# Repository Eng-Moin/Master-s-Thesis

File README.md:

# Master-s-Thesis

[Master-s-Thesis

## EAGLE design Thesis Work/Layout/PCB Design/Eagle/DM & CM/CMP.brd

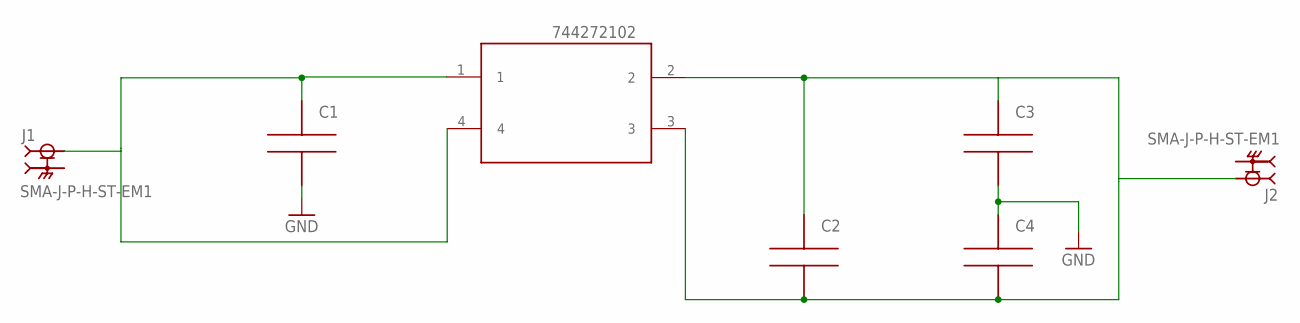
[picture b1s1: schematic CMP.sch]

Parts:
C1, C2, C3, C4: CAPA1206; FGJGFN
CHIP: CHOKE
J1, J2: SMA-J-P-H-ST-EM1; SAMTEC_SMA-J-P-H-ST-EM1

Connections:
GND: C1.1, C3.1, C4.2
unnamed: C2.1, C2.2, C3.2, C4.1, CHIP.2, CHIP.3, J2.1
unnamed: C1.2, CHIP.1, CHIP.4, J1.1

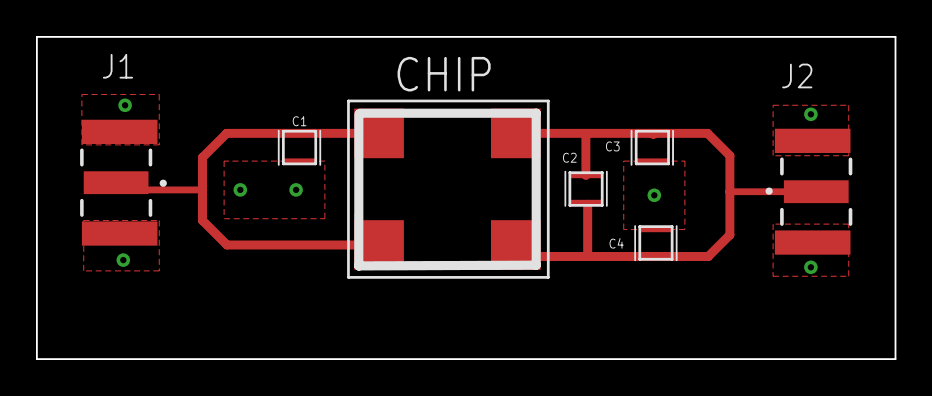
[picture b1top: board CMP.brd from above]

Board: 2 copper layers, 47.7 x 17.9 mm, 7 parts (0 on the bottom side), 3 nets.

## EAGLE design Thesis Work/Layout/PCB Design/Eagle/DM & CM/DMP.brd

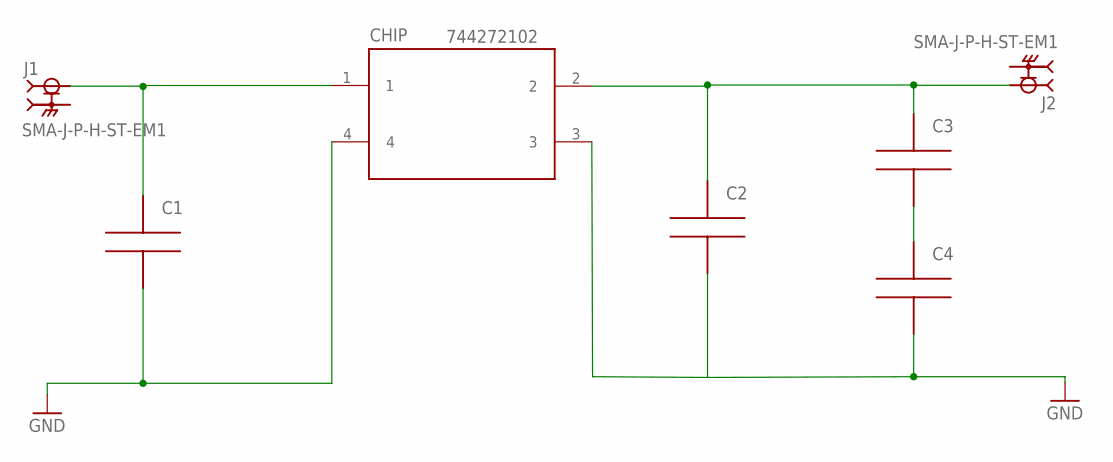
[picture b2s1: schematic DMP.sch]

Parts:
C1, C2, C3, C4: CAPA1206; FGJGFN
CHIP: CHOKE
J1, J2: SMA-J-P-H-ST-EM1; SAMTEC_SMA-J-P-H-ST-EM1

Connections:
GND: C1.1, C2.1, C4.1, CHIP.3, CHIP.4
unnamed: C1.2, CHIP.1, J1.1
unnamed: C2.2, C3.2, CHIP.2, J2.1
unnamed: C3.1, C4.2

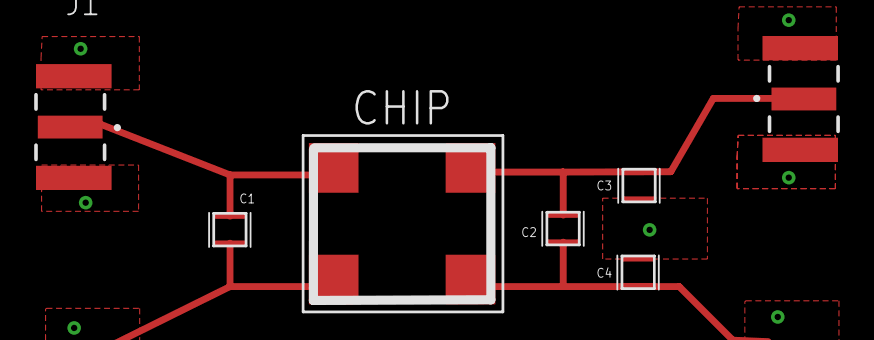
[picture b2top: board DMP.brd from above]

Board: 2 copper layers, 7 parts (0 on the bottom side), 4 nets.

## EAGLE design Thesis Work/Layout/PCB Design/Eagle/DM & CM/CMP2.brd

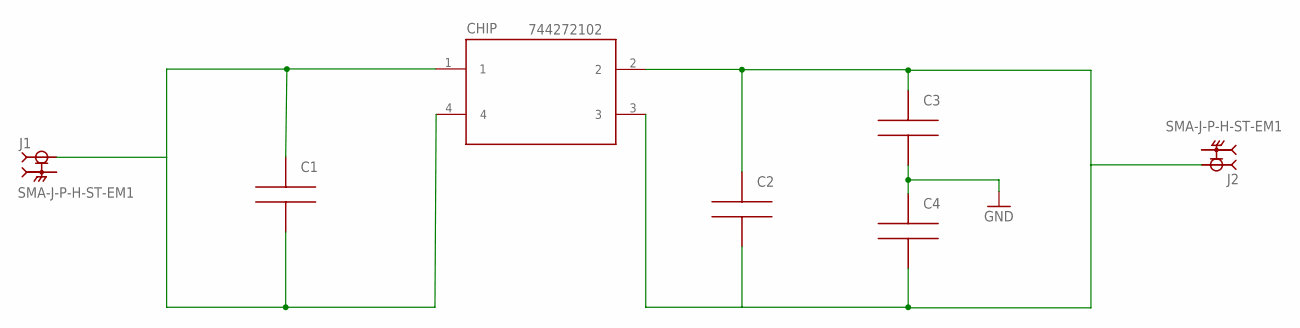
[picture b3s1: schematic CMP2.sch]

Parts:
C1, C2, C3, C4: CAPA1206; FGJGFN
CHIP: CHOKE
J1, J2: SMA-J-P-H-ST-EM1; SAMTEC_SMA-J-P-H-ST-EM1

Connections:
GND: C3.1, C4.2
unnamed: C1.1, C1.2, CHIP.1, CHIP.4, J1.1
unnamed: C2.1, C2.2, C3.2, C4.1, CHIP.2, CHIP.3, J2.1

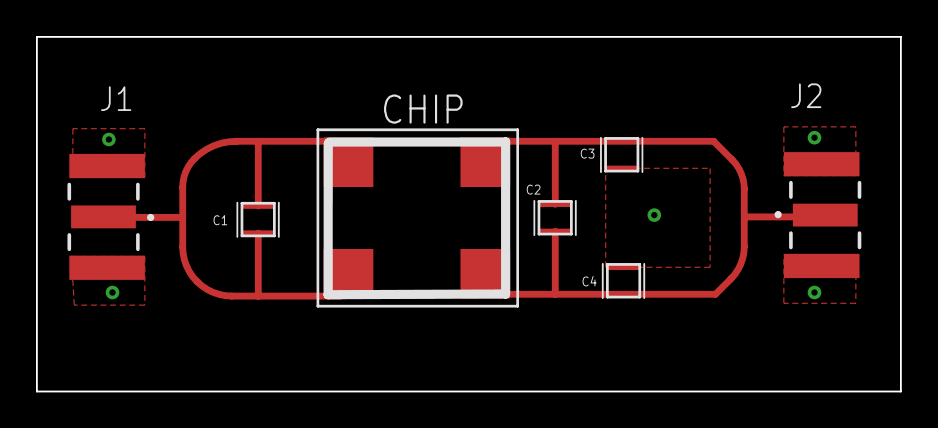
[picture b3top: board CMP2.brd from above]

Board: 2 copper layers, 48.0 x 19.7 mm, 7 parts (0 on the bottom side), 3 nets.

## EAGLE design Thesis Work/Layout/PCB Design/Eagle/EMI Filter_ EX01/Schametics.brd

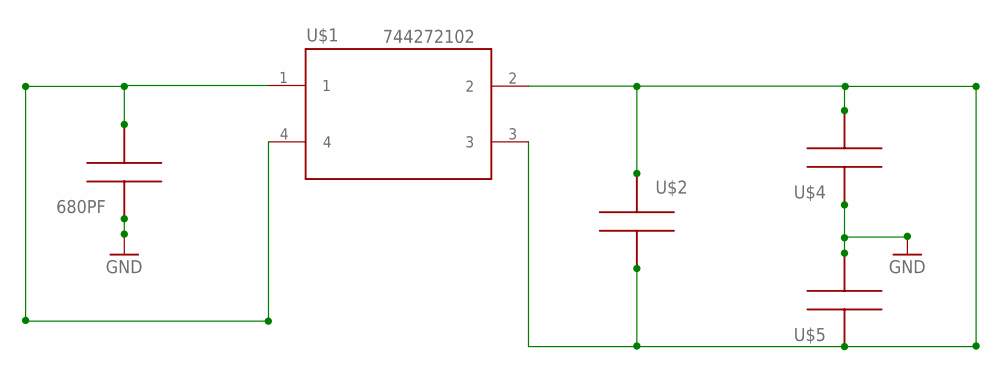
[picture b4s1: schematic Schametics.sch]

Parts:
680PF: CAPA1206; FGJGFN
U$1: CHOKE
U$2, U$4, U$5: CAPA1206; FGJGFN

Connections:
GND: 680PF.2
unnamed: 680PF.1, U$1.4
unnamed: U$4.2, U$5.1
unnamed: U$1.3, U$4.1, U$5.2

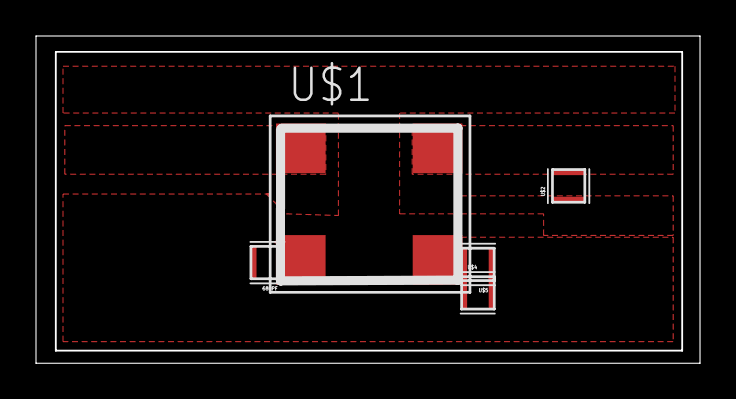
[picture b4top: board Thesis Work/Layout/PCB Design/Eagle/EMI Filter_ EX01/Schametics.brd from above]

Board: 2 copper layers, 36.9 x 18.2 mm, 5 parts (0 on the bottom side), 3 nets.

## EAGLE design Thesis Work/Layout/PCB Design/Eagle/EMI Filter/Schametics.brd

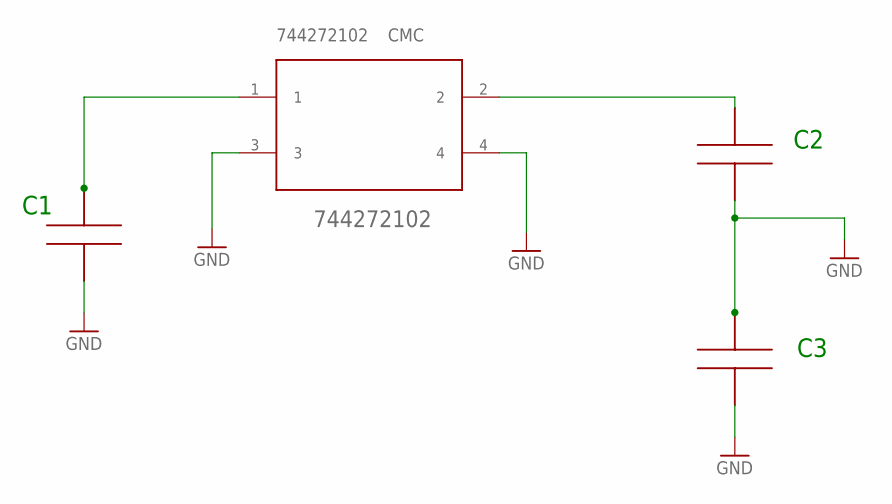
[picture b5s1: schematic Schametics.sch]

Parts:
744272102: CHOKE
U$1: 1500pF; FGJGFN
U$2, U$3: CAPA1210; FGJGFN

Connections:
GND: 744272102.3, 744272102.4, U$1.1, U$2.1, U$3.1, U$3.2
unnamed: 744272102.1, U$1.2
unnamed: 744272102.2, U$2.2

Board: 2 copper layers, 4 parts (0 on the bottom side), 3 nets, no tracks yet.

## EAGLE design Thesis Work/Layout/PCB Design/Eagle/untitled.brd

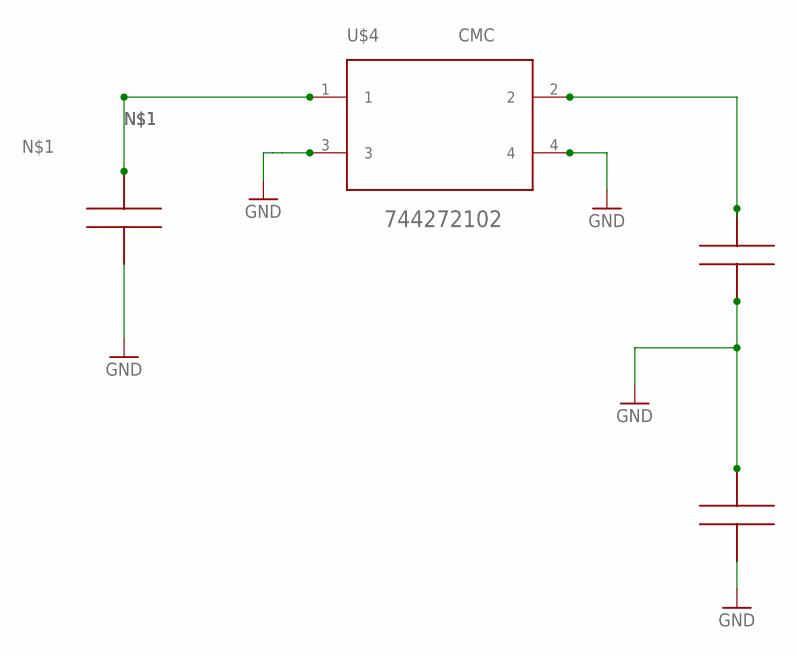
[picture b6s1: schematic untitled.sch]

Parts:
C1, C2: CAPA1210; FGJGFN
U$3: CAPA1210; FGJGFN
U$4: CHOKE

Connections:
GND: C1.1, C2.1, U$3.1, U$3.2, U$4.3, U$4.4
unnamed: C1.2, U$4.1
unnamed: C2.2, U$4.2

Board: 2 copper layers, 4 parts (0 on the bottom side), 3 nets, no tracks yet.

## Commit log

2021-05-05 First to Commit
2021-05-05 first
